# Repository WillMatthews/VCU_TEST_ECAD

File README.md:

# VCU TEST ECAD
VCU to Beaglebone breakout hardware for testing the VCU, and future continuous integration work.

## Schematic and PCB

The project is made in KiCad. Which can be obtained for free! [KiCad 5.0](http://kicad-pcb.org/download/)
All project files are in the `Kicad/` subdirectory.

## Components

The design is made for power supply of 5V from either a MicroUSB or USBC power supply.
The target current consumption by this device is 1A under load, but may be higher.

We use a SAM e70 Xplained evaluation kit as the VCU.

A Beaglebone black as the test host.

### CAN
We use TCAN1042 CAN transcievers.

Both on can0 of VCU and Beaglebone.

### RS232 (Motor Emulation)
We use MAX 3232 chips for:

LEFT: Beaglebone UART2, VCU UART 1

RIGHT: Beaglebone UART4, VCU UART 2

## Signals
See pinreference_bb_vcu.ods for which beaglebone GPIOs go where (needs updating)!

## Continuous Integration
We plan to use Jenkins CI, but this is yet to be figured out and made a reality.

## Future Work

We also have plans for a DAC daughterboard to supply analogue signals to the sensors on VCU, reference also on above document.

THINGS TO DO:
- [ ] Does TLV5631 actually have SPI or is the datasheet blatantly lying to my face?
  - Now made a "daugherboard" project if required.
- [x] Put correct CAN chips
- [ ] Confirm design with team
- [x] Layout
- [x] GET LAYOUT FOR THE VCU PINS !!! Cannot find anywhere !!!
- [ ] Start test software repo
- [ ] Better documentation for pins

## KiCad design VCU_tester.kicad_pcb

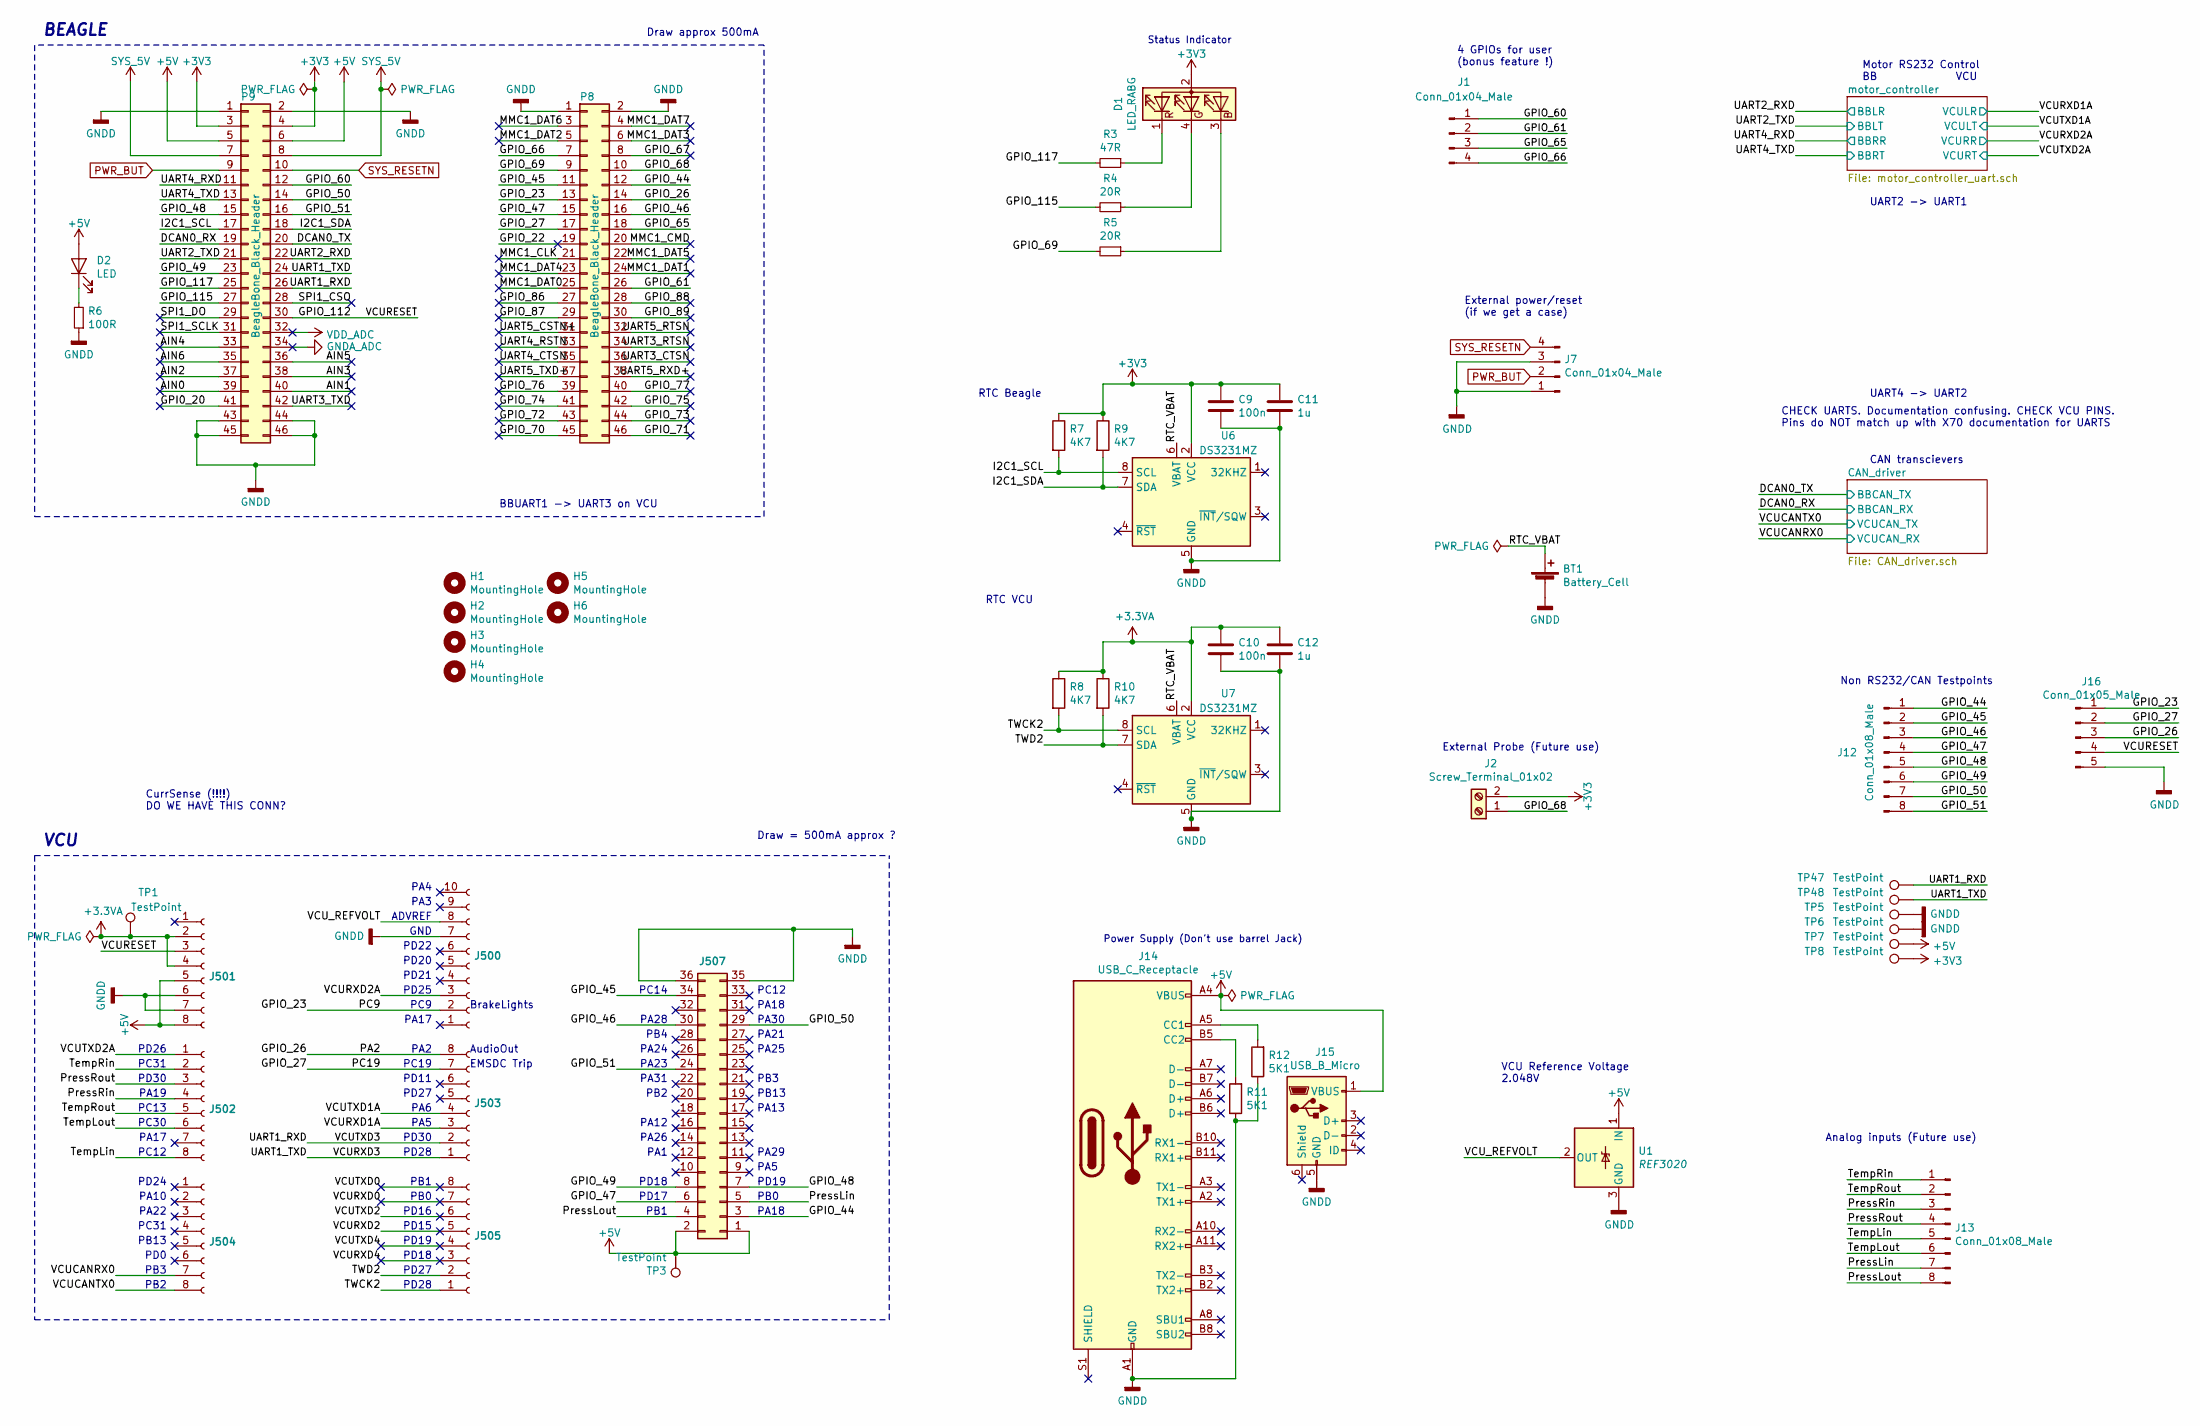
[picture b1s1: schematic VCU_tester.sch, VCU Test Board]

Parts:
BT1: Battery_Cell; BatteryHolder_Keystone_1060_1x2032; Part BU2032SM-FH-GCT-ND
C9, C10: 100n; C_0805_2012Metric_Pad1.15x1.40mm_HandSolder
C11, C12: 1u; C_0805_2012Metric_Pad1.15x1.40mm_HandSolder
D1: LED_RABG; LED_D5.0mm-4_RGB; Part WP154A4SEJ3VBDZGW/CA
D2: LED; D_1210_3225Metric_Pad1.42x2.65mm_HandSolder; Part 516-2672-1-ND
H1, H2, H3, H4, H5, H6: MountingHole; MountingHole_3.2mm_M3_ISO7380_Pad
J1, J7: Conn_01x04_Male; PinHeader_1x04_P2.54mm_Vertical
J2: Screw_Terminal_01x02; TerminalBlock_bornier-2_P5.08mm; Part 282837-2
J12, J13: Conn_01x08_Male; PinHeader_1x08_P2.54mm_Vertical
J14: USB_C_Receptacle; USB_C_Receptacle_GCT_USB4085; Part 2073-USB4085-GF-ACT-ND
J15: USB_B_Micro; USB_Micro-B_Molex-105017-0001
J16: Conn_01x05_Male; PinHeader_1x05_P2.54mm_Vertical
J500: Conn_01x10_Female; PinSocket_1x10_P2.54mm_Vertical
J501, J502, J503, J504, J505: Conn_01x08_Female; PinSocket_1x08_P2.54mm_Vertical
J507: Conn_02x18_Odd_Even; PinSocket_2x18_P2.54mm_Vertical
P8, P9: BeagleBone_Black_Header; PinHeader_2x23_P2.54mm_Vertical_Flip
R3: 47R; R_0805_2012Metric_Pad1.15x1.40mm_HandSolder
R4, R5: 20R; R_0805_2012Metric_Pad1.15x1.40mm_HandSolder
R6: 100R; R_0805_2012Metric_Pad1.15x1.40mm_HandSolder
R7, R8, R9, R10: 4K7; R_0805_2012Metric_Pad1.15x1.40mm_HandSolder
R11, R12: 5K1; R_0805_2012Metric_Pad1.15x1.40mm_HandSolder
TP1, TP3, TP5, TP6, TP7, TP8, TP47, TP48: TestPoint; PinHeader_1x01_P2.54mm_Vertical
U1: REF3020; SOT-23; Part 296-26321-1-ND
U6, U7: DS3231MZ; SOIC-8_3.9x4.9mm_P1.27mm

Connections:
+3.3VA: C10.1, C12.1, J501.2, J501.4, R8.1, R10.1, TP1.1, U7.2 (VCC); also elsewhere on the board
+3V3: C9.1, C11.1, D1.2 (A), J2.2, P9.3, P9.4, R7.1, R9.1, TP8.1, U6.2 (VCC); also elsewhere on the board
+5V: D2.2 (A), J14.A4 (VBUS), J14.A9 (VBUS), J14.B4 (VBUS), J14.B9 (VBUS), J15.1 (VBUS), J501.5, J501.8, J507.1, J507.2, P9.5, P9.6, TP3.1, TP7.1, U1.1 (IN); also elsewhere on the board
/AIN0: P9.39
/AIN1: P9.40
/AIN2: P9.37
/AIN3: P9.38
/AIN4: P9.33
/AIN5: P9.36
/AIN6: P9.35
/DCAN0_RX: P9.19; also elsewhere on the board
/DCAN0_TX: P9.20; also elsewhere on the board
/GPI0_20: P9.41
/GPIO_22: P8.19
/GPIO_23: J16.1, J500.2, P8.13
/GPIO_26: J16.3, J503.8, P8.14
/GPIO_27: J16.2, J503.7, P8.17
/GPIO_44: J12.1, J507.3, P8.12
/GPIO_45: J12.2, J507.34, P8.11
/GPIO_46: J12.3, J507.30, P8.16
/GPIO_47: J12.4, J507.6, P8.15
/GPIO_48: J12.5, J507.7, P9.15
/GPIO_49: J12.6, J507.8, P9.23
/GPIO_50: J12.7, J507.29, P9.14
/GPIO_51: J12.8, J507.24, P9.16
/GPIO_60: J1.1, P9.12
/GPIO_61: J1.2, P8.26
/GPIO_65: J1.3, P8.18
/GPIO_66: J1.4, P8.7
/GPIO_67: P8.8
/GPIO_68: J2.1, P8.10
/GPIO_69: P8.9, R5.2
/GPIO_70: P8.45
/GPIO_71: P8.46
/GPIO_72: P8.43
/GPIO_73: P8.44
/GPIO_74: P8.41
/GPIO_75: P8.42
/GPIO_76: P8.39
/GPIO_77: P8.40
/GPIO_86: P8.27
/GPIO_87: P8.29
/GPIO_88: P8.28
/GPIO_89: P8.30
/GPIO_112: J16.4, J501.3, P9.30
/GPIO_115: P9.27, R4.2
/GPIO_117: P9.25, R3.2
/I2C1_SCL: P9.17, R7.2, U6.8 (SCL)
/I2C1_SDA: P9.18, R9.2, U6.7 (SDA)
/MMC1_CLK: P8.21
/MMC1_CMD: P8.20
/MMC1_DAT0: P8.25
/MMC1_DAT1: P8.24
/MMC1_DAT2: P8.5
/MMC1_DAT3: P8.6
/MMC1_DAT4: P8.23
/MMC1_DAT5: P8.22
/MMC1_DAT6: P8.3
/MMC1_DAT7: P8.4
/PressLin: J13.7, J507.5
/PressLout: J13.8, J507.4
/PressRin: J13.3, J502.4
/PressRout: J13.4, J502.3
/RTC_VBAT: BT1.1 (+), U6.6 (VBAT), U7.6 (VBAT)
/SPI1_CSO: P9.28
/SPI1_DO: P9.29
/SPI1_SCLK: P9.31
/TWCK2: J505.1, R8.2, U7.8 (SCL)
/TWD2: J505.2, R10.2, U7.7 (SDA)
/TempLin: J13.5, J502.8
/TempLout: J13.6, J502.6
/TempRin: J13.1, J502.2
/TempRout: J13.2, J502.5
/UART1_RXD: J503.2, P9.26, TP47.1
/UART1_TXD: J503.1, P9.24, TP48.1
/UART2_RXD: P9.22; also elsewhere on the board
/UART2_TXD: P9.21; also elsewhere on the board
/UART3_CTSN: P8.36
/UART3_RTSN: P8.34
/UART3_TXD: P9.42
/UART4_CTSN: P8.35
/UART4_RSTN: P8.33
/UART4_RXD: P9.11; also elsewhere on the board
/UART4_TXD: P9.13; also elsewhere on the board
/UART5_CSTN+: P8.31
/UART5_RTSN: P8.32
/UART5_RXD+: P8.38
/UART5_TXD+: P8.37
/VCUCANRX0: J504.7; also elsewhere on the board
/VCUCANTX0: J504.8; also elsewhere on the board
/VCURXD0: J505.7
/VCURXD1A: J503.3; also elsewhere on the board
/VCURXD2: J505.5
/VCURXD2A: J500.3; also elsewhere on the board
/VCURXD4: J505.3
/VCUTXD0: J505.8
/VCUTXD1A: J503.4; also elsewhere on the board
/VCUTXD2: J505.6
/VCUTXD2A: J502.1; also elsewhere on the board
/VCUTXD4: J505.4
/VCU_REFVOLT: J500.8, U1.2 (OUT)
GNDA_ADC: P9.34
GNDD: BT1.2 (-), C9.2, C10.2, C11.2, C12.2, J7.1, J7.3, J14.A1 (GND), J14.A12 (GND), J14.B1 (GND), J14.B12 (GND), J15.5 (GND), J16.5, J500.7, J501.6, J501.7, J507.35, J507.36, P8.1, P8.2, P9.1, P9.2, P9.43, P9.44, P9.45, P9.46, R6.1, R11.1, R12.1, TP5.1, TP6.1, U1.3 (GND), U6.5 (GND), U7.5 (GND); also elsewhere on the board
unnamed: D1.1 (RK), R3.1
unnamed: D1.3 (BK), R5.1
unnamed: D1.4 (GK), R4.1
unnamed: D2.1 (K), R6.2
unnamed: J14.A5 (CC1), R12.2
unnamed: J14.B5 (CC2), R11.2
PWR_BUT: J7.2, P9.9
SYS_5V: P9.7, P9.8
SYS_RESETN: J7.4, P9.10
VDD_ADC: P9.32

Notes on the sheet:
4 GPIOs for user (bonus feature !)
UART2 -> UART1
UART4 -> UART2
Motor RS232 Control BB VCU
BBUART1 -> UART3 on VCU
CAN transcievers
BEAGLE
VCU
Status Indicator
CHECK UARTS. Documentation confusing. CHECK VCU PINS. Pins do NOT match up with X70 documentation for UARTS
CurrSense (!!!!) DO WE HAVE THIS CONN?
Non RS232/CAN Testpoints
External power/reset (if we get a case)
Draw = 500mA approx ?
Draw approx 500mA
Power Supply (Don't use barrel Jack)
RTC Beagle
RTC VCU
VCU Reference Voltage 2.048V
External Probe (Future use)
Analog inputs (Future use)
AudioOut
EMSDC Trip
PA4
PA3
ADVREF
GND
PD22
PD20
PD21
PD25
PC9
PA17
PA2
PC19
PD11
PD27
PA6
PA5
PD30

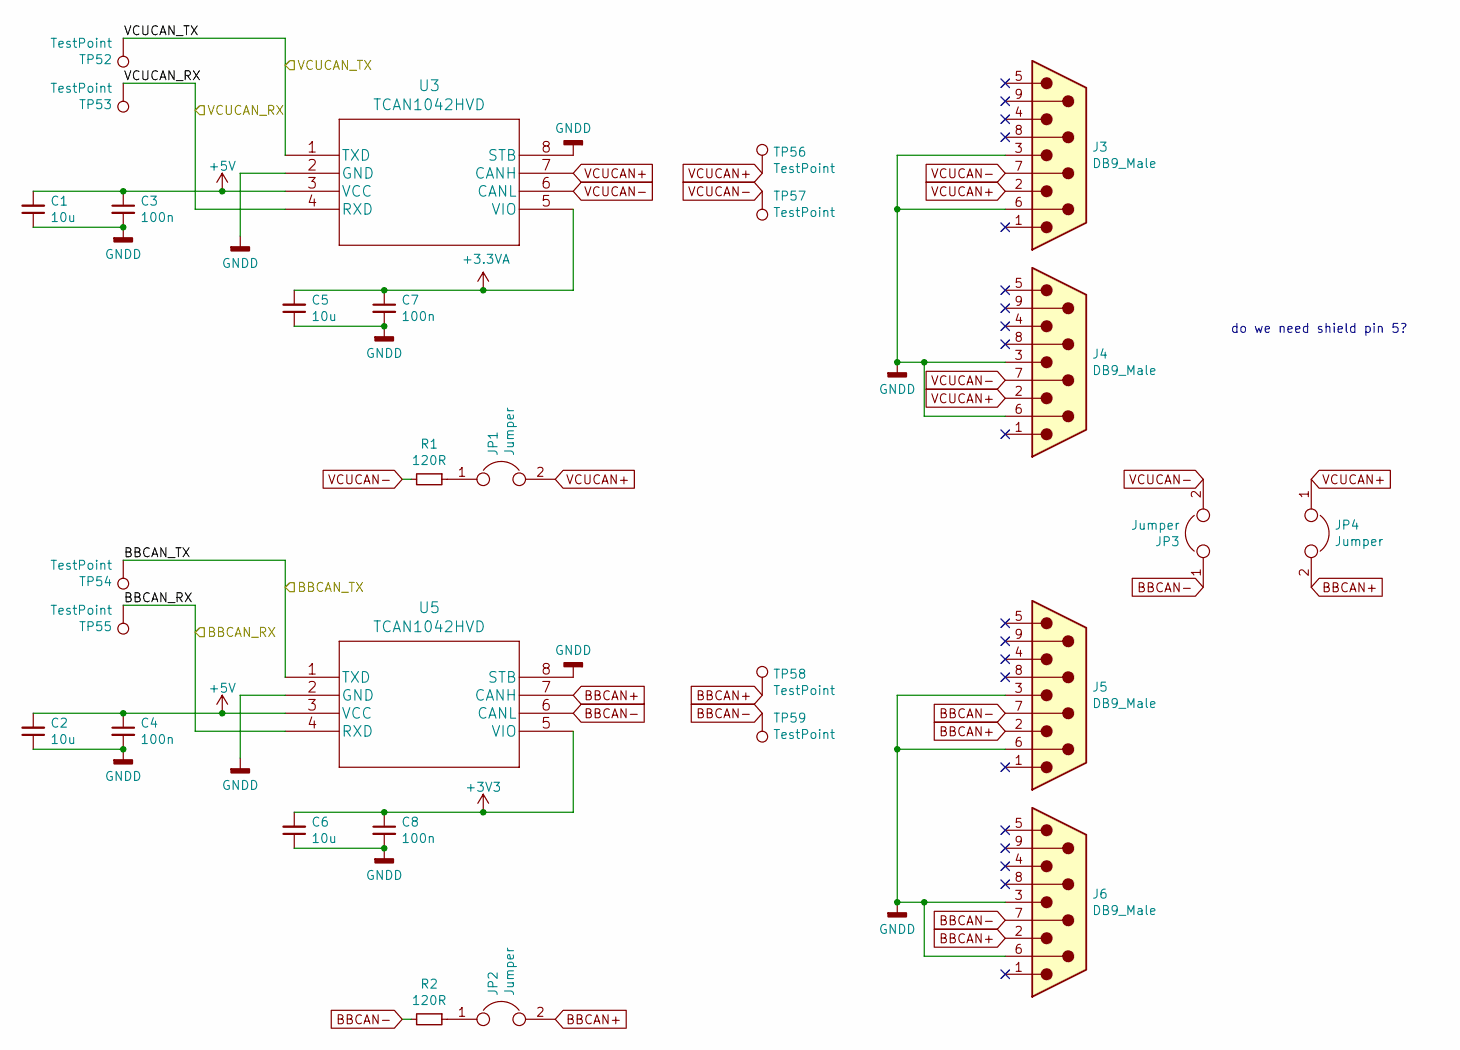
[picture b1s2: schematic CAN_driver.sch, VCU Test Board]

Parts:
C1, C2, C5, C6: 10u; C_0805_2012Metric_Pad1.15x1.40mm_HandSolder
C3, C4, C7, C8: 100n; C_0805_2012Metric_Pad1.15x1.40mm_HandSolder
J3, J4, J5, J6: DB9_Male; DSUB-9_Male_Vertical_P2.77x2.84mm_MountingHoles; Part 5747840-3
JP1, JP2, JP3, JP4: Jumper; PinHeader_1x03_P2.00mm_Vertical; Part SPN02SXCN-RC
R1, R2: 120R; R_0805_2012Metric_Pad1.15x1.40mm_HandSolder
TP52, TP53, TP54, TP55, TP56, TP57, TP58, TP59: TestPoint; PinHeader_1x01_P2.54mm_Vertical
U3, U5: TCAN1042HVD; SO-8_3.9x4.9mm_P1.27mm; Part 296-48672-1-ND

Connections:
+3.3VA: C5.2, C7.1, U3.5 (VIO); also elsewhere on the board
+3V3: C6.2, C8.1, U5.5 (VIO); also elsewhere on the board
+5V: C1.2, C2.2, C3.1, C4.1, U3.3 (VCC), U5.3 (VCC); also elsewhere on the board
/DCAN0_RX: TP55.1, U5.4 (RXD); also elsewhere on the board
/DCAN0_TX: TP54.1, U5.1 (TXD); also elsewhere on the board
/VCUCANRX0: TP53.1, U3.4 (RXD); also elsewhere on the board
/VCUCANTX0: TP52.1, U3.1 (TXD); also elsewhere on the board
GNDD: C1.1, C2.1, C3.2, C4.2, C5.1, C6.1, C7.2, C8.2, J3.3, J3.6, J4.3, J4.6, J5.3, J5.6, J6.3, J6.6, U3.2 (GND), U3.8 (STB), U5.2 (GND), U5.8 (STB); also elsewhere on the board
unnamed: JP1.1, R1.1
unnamed: JP2.1, R2.1

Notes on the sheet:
do we need shield pin 5?

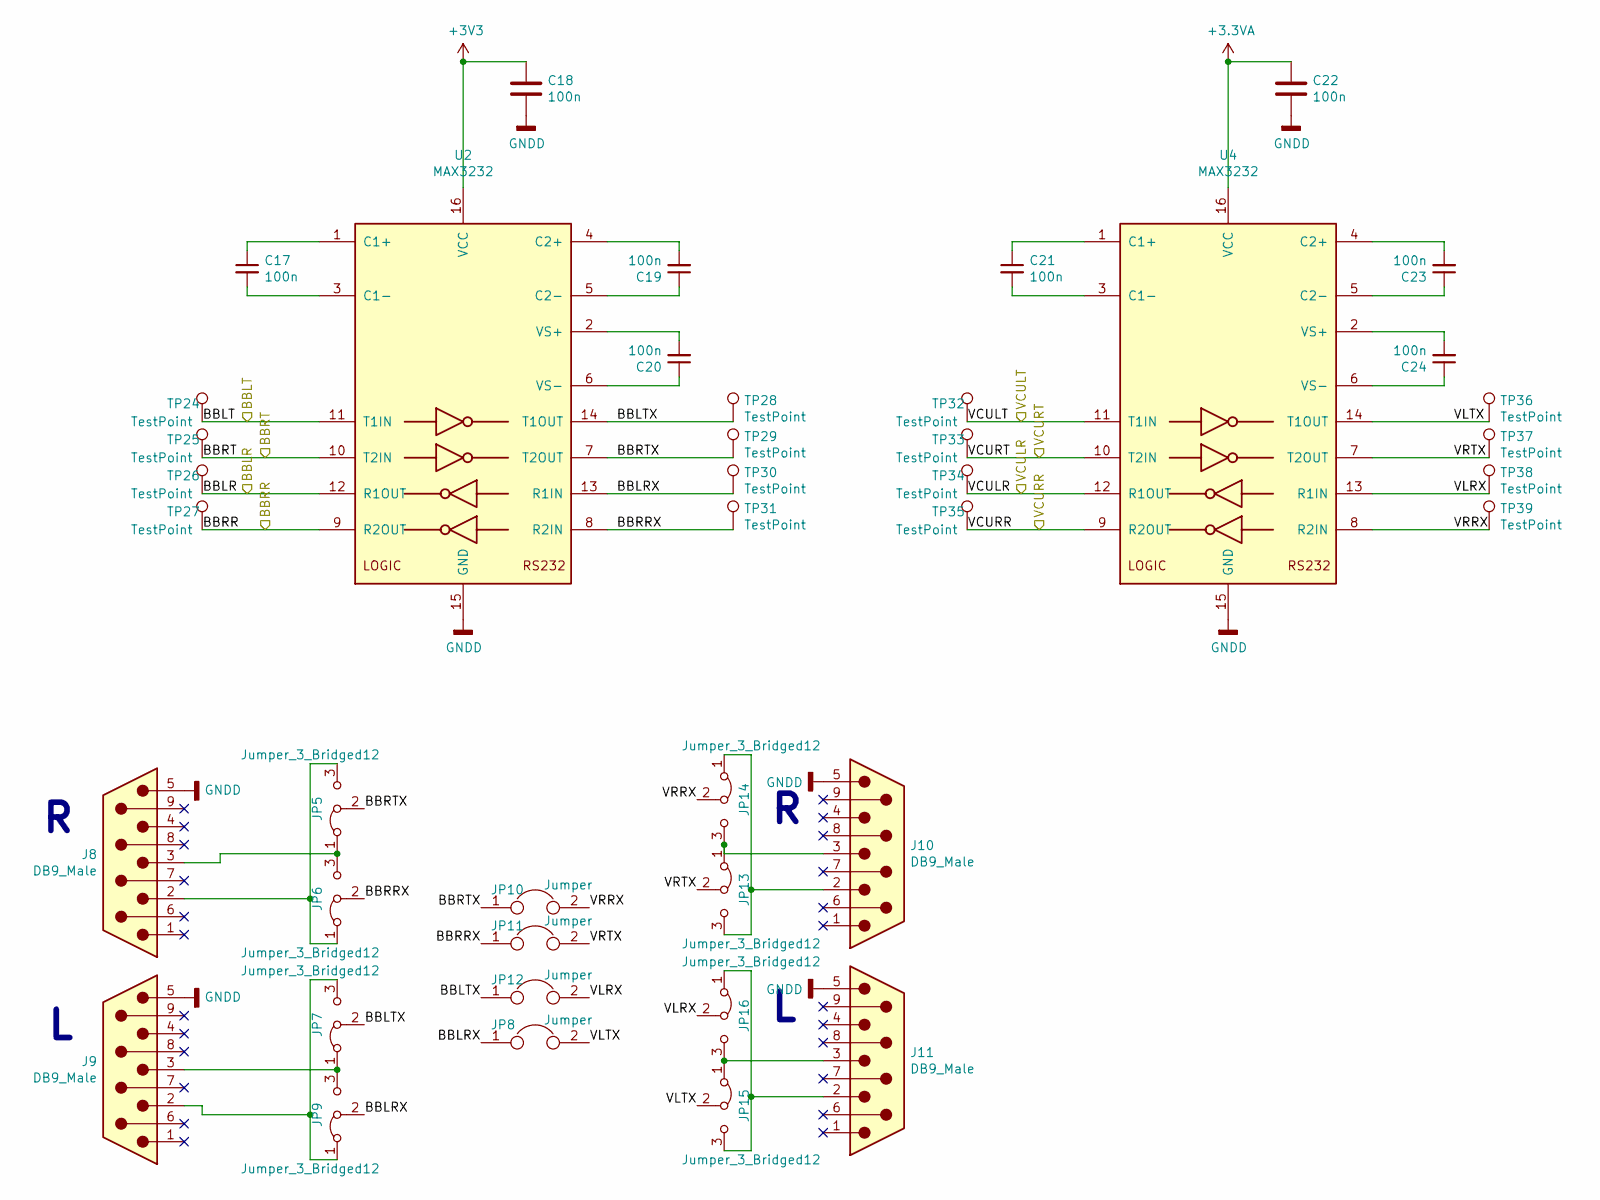
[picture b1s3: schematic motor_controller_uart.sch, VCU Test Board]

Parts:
C17, C18, C19, C20, C21, C22, C23, C24: 100n; C_0805_2012Metric_Pad1.15x1.40mm_HandSolder
J8, J9, J10, J11: DB9_Male; DSUB-9_Male_Vertical_P2.77x2.84mm_MountingHoles; Part 5747840-3
JP5, JP6, JP7, JP9, JP13, JP14, JP15, JP16: Jumper_3_Bridged12; PinHeader_1x03_P2.00mm_Vertical; Part SPN02SXCN-RC
JP8, JP10, JP11, JP12: Jumper; PinHeader_1x03_P2.00mm_Vertical; Part SPN02SXCN-RC
TP24, TP25, TP26, TP27, TP28, TP29, TP30, TP31, TP32, TP33, TP34, TP35, TP36, TP37, TP38, TP39: TestPoint; PinHeader_1x01_P2.54mm_Vertical
U2, U4: MAX3232; SOIC-16_3.9x9.9mm_P1.27mm; Part MAX3232CSE+TCT-ND

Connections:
+3.3VA: C22.1, U4.16 (VCC); also elsewhere on the board
+3V3: C18.1, U2.16 (VCC); also elsewhere on the board
/UART2_RXD: TP26.1, U2.12 (R1OUT); also elsewhere on the board
/UART2_TXD: TP24.1, U2.11 (T1IN); also elsewhere on the board
/UART4_RXD: TP27.1, U2.9 (R2OUT); also elsewhere on the board
/UART4_TXD: TP25.1, U2.10 (T2IN); also elsewhere on the board
/VCURXD1A: TP34.1, U4.12 (R1OUT); also elsewhere on the board
/VCURXD2A: TP35.1, U4.9 (R2OUT); also elsewhere on the board
/VCUTXD1A: TP32.1, U4.11 (T1IN); also elsewhere on the board
/VCUTXD2A: TP33.1, U4.10 (T2IN); also elsewhere on the board
/motor_controller/BBLRX: JP8.1, JP9.2 (C), TP30.1, U2.13 (R1IN)
/motor_controller/BBLTX: JP7.2 (C), JP12.1, TP28.1, U2.14 (T1OUT)
/motor_controller/BBRRX: JP6.2 (C), JP11.1, TP31.1, U2.8 (R2IN)
/motor_controller/BBRTX: JP5.2 (C), JP10.1, TP29.1, U2.7 (T2OUT)
/motor_controller/VLRX: JP12.2, JP16.2 (C), TP38.1, U4.13 (R1IN)
/motor_controller/VLTX: JP8.2, JP15.2 (C), TP36.1, U4.14 (T1OUT)
/motor_controller/VRRX: JP10.2, JP14.2 (C), TP39.1, U4.8 (R2IN)
/motor_controller/VRTX: JP11.2, JP13.2 (C), TP37.1, U4.7 (T2OUT)
GNDD: C18.2, C22.2, J8.5, J9.5, J10.5, J11.5, U2.15 (GND), U4.15 (GND); also elsewhere on the board
unnamed: C17.1, U2.1 (C1+)
unnamed: C17.2, U2.3 (C1-)
unnamed: C19.1, U2.5 (C2-)
unnamed: C19.2, U2.4 (C2+)
unnamed: C20.1, U2.6 (VS-)
unnamed: C20.2, U2.2 (VS+)
unnamed: C21.1, U4.1 (C1+)
unnamed: C21.2, U4.3 (C1-)
unnamed: C23.1, U4.5 (C2-)
unnamed: C23.2, U4.4 (C2+)
unnamed: C24.1, U4.6 (VS-)
unnamed: C24.2, U4.2 (VS+)
unnamed: J8.2, JP5.3 (B), JP6.1 (A)
unnamed: J8.3, JP5.1 (A), JP6.3 (B)
unnamed: J9.2, JP7.3 (B), JP9.1 (A)
unnamed: J9.3, JP7.1 (A), JP9.3 (B)
unnamed: J10.2, JP13.3 (B), JP14.1 (A)
unnamed: J10.3, JP13.1 (A), JP14.3 (B)
unnamed: J11.2, JP15.3 (B), JP16.1 (A)
unnamed: J11.3, JP15.1 (A), JP16.3 (B)

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
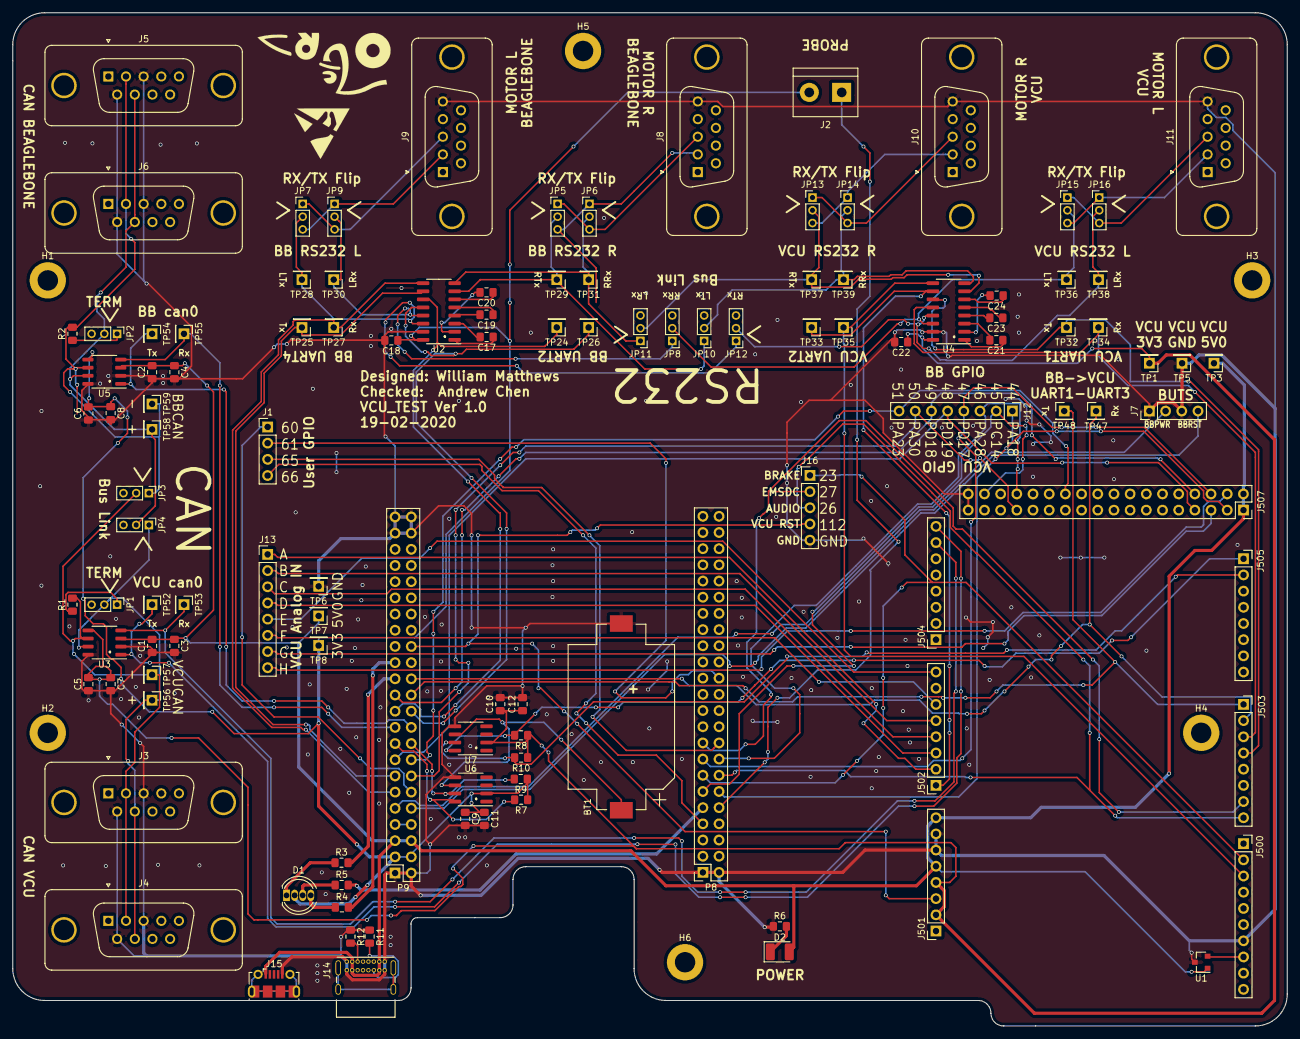
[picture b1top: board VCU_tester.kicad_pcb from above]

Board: 2 copper layers, 200.0 x 159.0 mm, 121 parts (0 on the bottom side), 95 nets.

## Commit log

2020-02-12 initial commit, BB black template
2020-02-12 CAN parts added, rs232 parts added, gpio added
2020-02-13 added vcu pinout, still lots needs doing
2020-02-13 added more vcu pinout, just need to route UART, figure out GPIO problem
2020-02-13 vcu pinout done
2020-02-14 added pin names vcu, rs232 mcguffins, losing hope
2020-02-14 misread diagram.. fixed
2020-02-15 sleep isn't real. Fixed pins. DAC hell. Nearly done on schematic.
2020-02-15 no connects and documentation
2020-02-15 forgot markdown formatting
2020-02-16 changed CAN chips
2020-02-16 removed dac, added jumpers, ready for parting up
2020-02-16 parts assigned, layout started, CAN and RS232 sides done
2020-02-16 added worksheet, shuffled board around to make it smaller
2020-02-16 pins corrected, RTC added
2020-02-17 routing start
2020-02-17 cant remember what I added Im tired
2020-02-17 added comments
2020-02-17 same70-xpld footprint
2020-02-17 beaglebone footprints
2020-02-17 de9 footprint
2020-02-17 placed vcu and beaglebone
2020-02-18 new, compact (and sexy) design
2020-02-18 forgot to save schematic
2020-02-18 fix sch vcu connections
2020-02-18 fix sch beaglebone connections
2020-02-18 vcu & bb 3d models
2020-02-19 Lots of layout, power bus
2020-02-19 decouple caps, moved testpoint for usb access, tcan footprints
2020-02-19 better routing, tcan footprint, mount holes + silkscreen
2020-02-20 reassigned brake, emsdc, audio vcurst, better testpoint
2020-02-21 add decouple caps, add gpios
2020-02-21 silkscreen, WE NEED TO CHECK CAN DB9
2020-02-21 rs232/can fix
2020-02-21 rs232 fix
2020-02-21 remove comments
2020-02-21 remove more comments
2020-02-21 silkscreen fix
2020-02-21 silkscreen fix2, ready to send off?
2020-02-21 gerbers and pdfs
2020-02-21 CAN pin fix, need to ground pour and done
2020-02-21 ground plane, checked, ready to go?
2020-02-22 silkscreen + neater copper fills, ready to go?
2020-02-22 clean fab notes
2020-02-22 add board image
2020-02-22 add documentation
2020-02-22 tidy up
2024-07-17 [ImgBot] Optimize images
    *Total -- 553.29kb -> 477.66kb (13.67%)
    /Kicad/logo.png -- 9.48kb -> 4.99kb (47.37%)
    /img/board.png -- 543.81kb -> 472.67kb (13.08%)
